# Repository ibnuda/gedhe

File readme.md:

# Gedhe

It's a split columnar-stagger keyboard that I made for one of
the [mahr](https://en.wikipedia.org/wiki/Mahr) for my wife.

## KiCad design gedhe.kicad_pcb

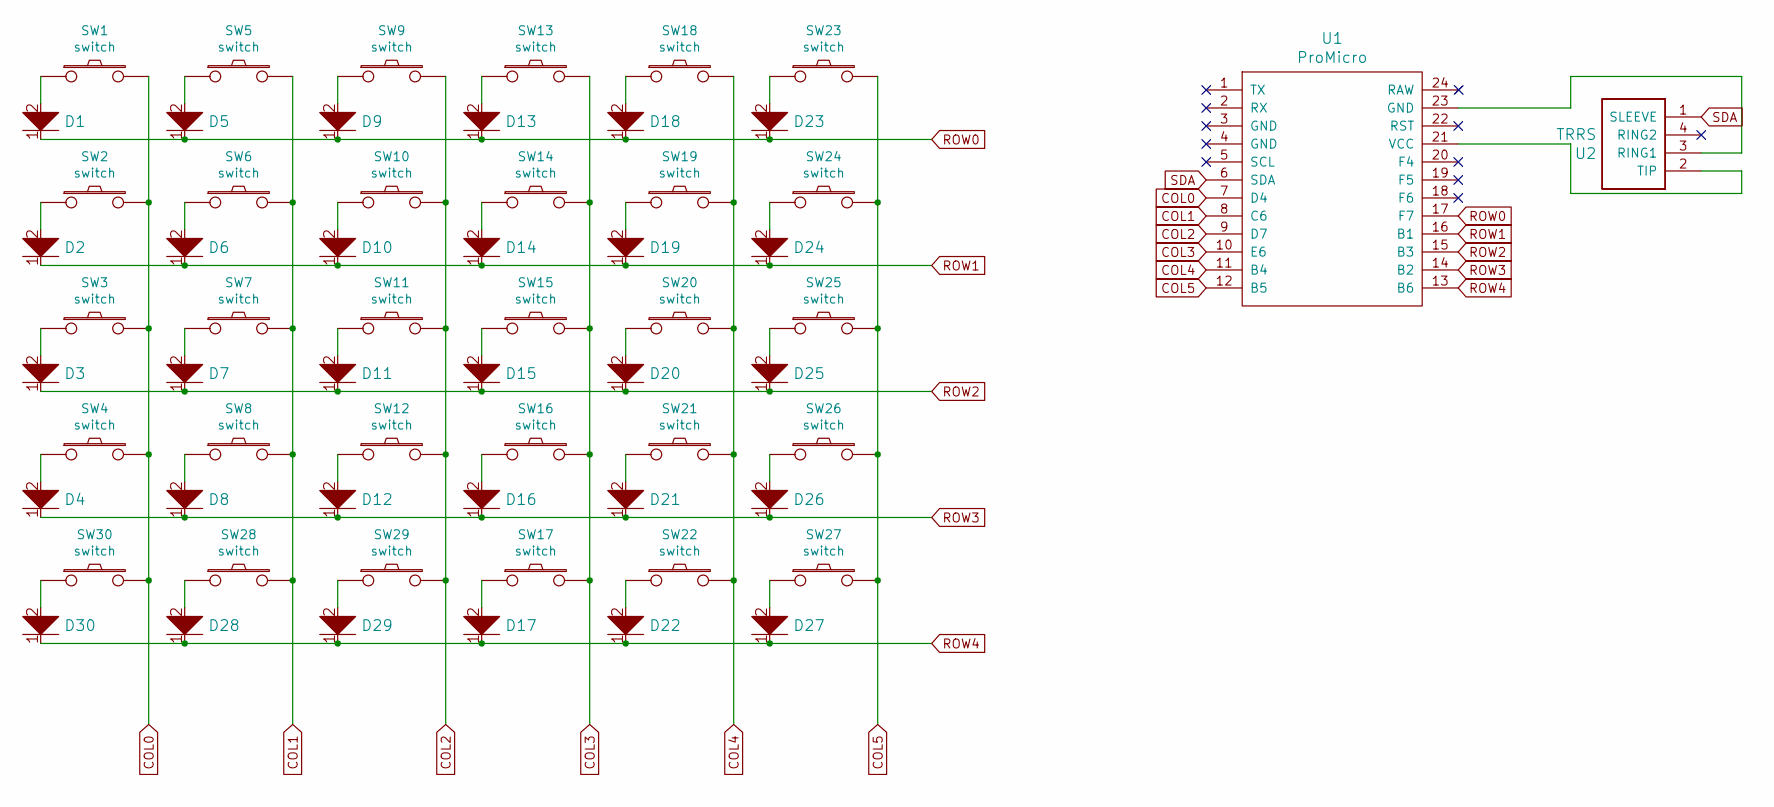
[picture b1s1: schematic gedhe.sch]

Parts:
D1, D2, D3, D4, D5, D6, D7, D8, D9, D10, D11, D12, D13, D14, D15, D16, D17, D18, D19, D20, D21, D22, D23, D24, D25, D26, D27, D28, D29, D30: D; diode
SW1, SW2, SW3, SW4, SW5, SW6, SW7, SW8, SW9, SW10, SW11, SW12, SW13, SW14, SW15, SW16, SW17, SW18, SW19, SW20, SW21, SW22, SW23, SW24, SW25, SW26, SW27, SW28, SW29, SW30: switch; 1u-dual
U1: ProMicro; promicro
U2: TRRS; trrs

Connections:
COL0: SW1.2, SW2.2, SW3.2, SW4.2, SW30.2, U1.7 (D4)
COL1: SW5.2, SW6.2, SW7.2, SW8.2, SW28.2, U1.8 (C6)
COL2: SW9.2, SW10.2, SW11.2, SW12.2, SW29.2, U1.9 (D7)
COL3: SW13.2, SW14.2, SW15.2, SW16.2, SW17.2, U1.10 (E6)
COL4: SW18.2, SW19.2, SW20.2, SW21.2, SW22.2, U1.11 (B4)
COL5: SW23.2, SW24.2, SW25.2, SW26.2, SW27.2, U1.12 (B5)
unnamed: D1.2, SW1.1
unnamed: D2.2, SW2.1
unnamed: D3.2, SW3.1
unnamed: D4.2, SW4.1
unnamed: D5.2, SW5.1
unnamed: D6.2, SW6.1
unnamed: D7.2, SW7.1
unnamed: D8.2, SW8.1
unnamed: D9.2, SW9.1
unnamed: D10.2, SW10.1
unnamed: D11.2, SW11.1
unnamed: D12.2, SW12.1
unnamed: D13.2, SW13.1
unnamed: D14.2, SW14.1
unnamed: D15.2, SW15.1
unnamed: D16.2, SW16.1
unnamed: D17.2, SW17.1
unnamed: D18.2, SW18.1
unnamed: D19.2, SW19.1
unnamed: D20.2, SW20.1
unnamed: D21.2, SW21.1
unnamed: D22.2, SW22.1
unnamed: D23.2, SW23.1
unnamed: D24.2, SW24.1
unnamed: D25.2, SW25.1
unnamed: D26.2, SW26.1
unnamed: D27.2, SW27.1
unnamed: D28.2, SW28.1
unnamed: D29.2, SW29.1
unnamed: D30.2, SW30.1
unnamed: U1.21 (VCC), U2.2 (TIP)
unnamed: U1.23 (GND), U2.3 (RING1)
ROW0: D1.1, D5.1, D9.1, D13.1, D18.1, D23.1, U1.17 (F7)
ROW1: D2.1, D6.1, D10.1, D14.1, D19.1, D24.1, U1.16 (B1)
ROW2: D3.1, D7.1, D11.1, D15.1, D20.1, D25.1, U1.15 (B3)
ROW3: D4.1, D8.1, D12.1, D16.1, D21.1, D26.1, U1.14 (B2)
ROW4: D17.1, D22.1, D27.1, D28.1, D29.1, D30.1, U1.13 (B6)
SDA: U1.6 (SDA), U2.1 (SLEEVE)

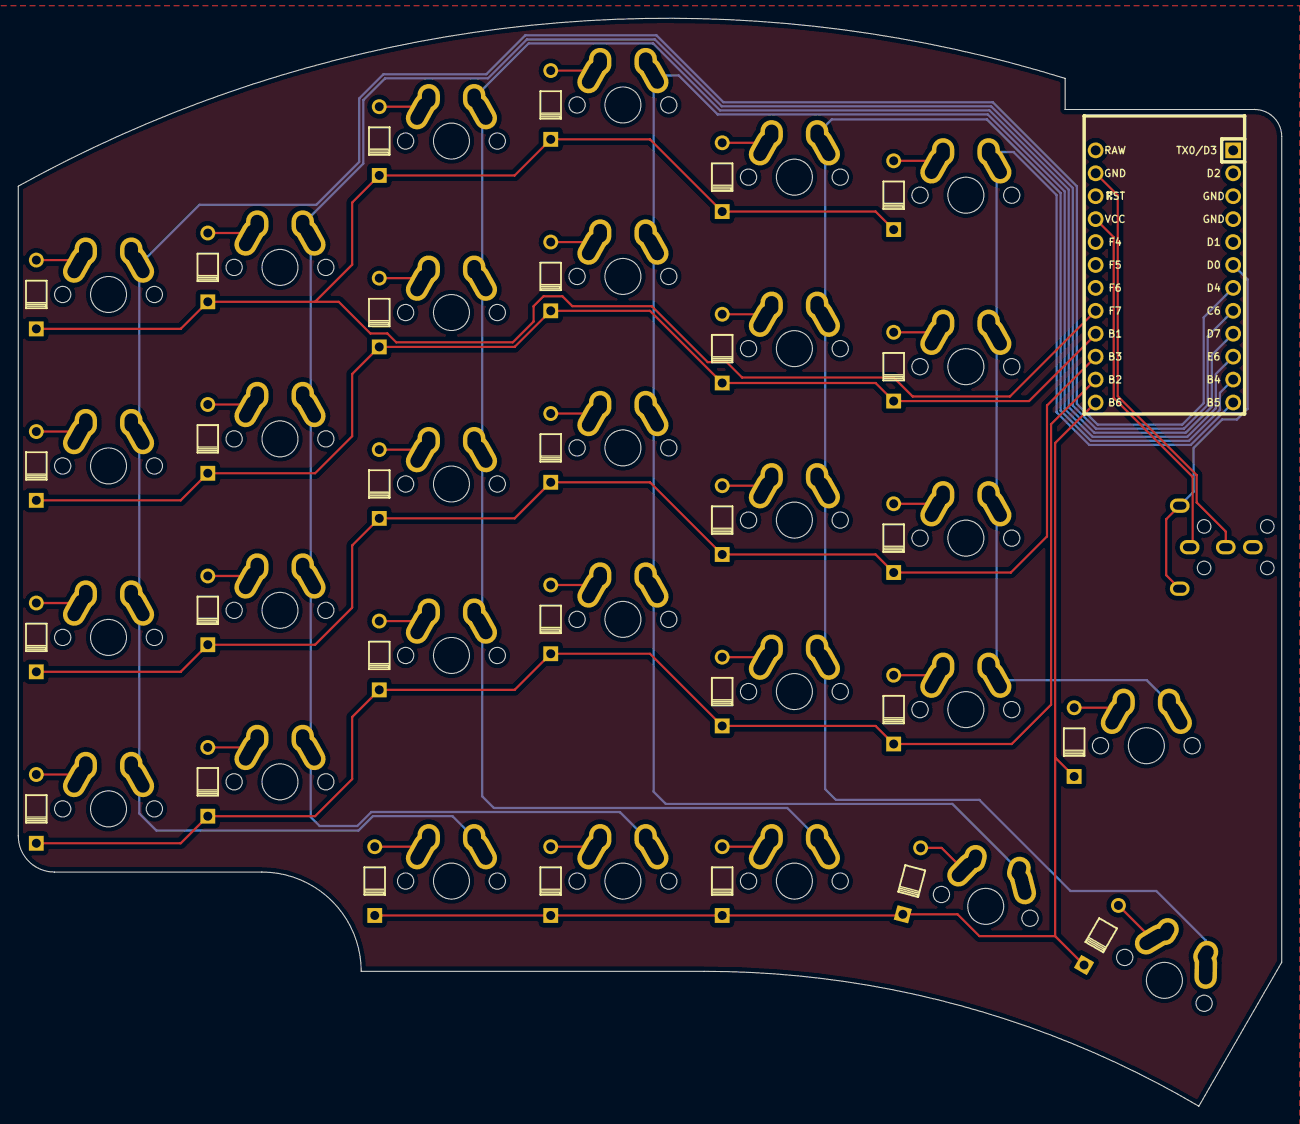
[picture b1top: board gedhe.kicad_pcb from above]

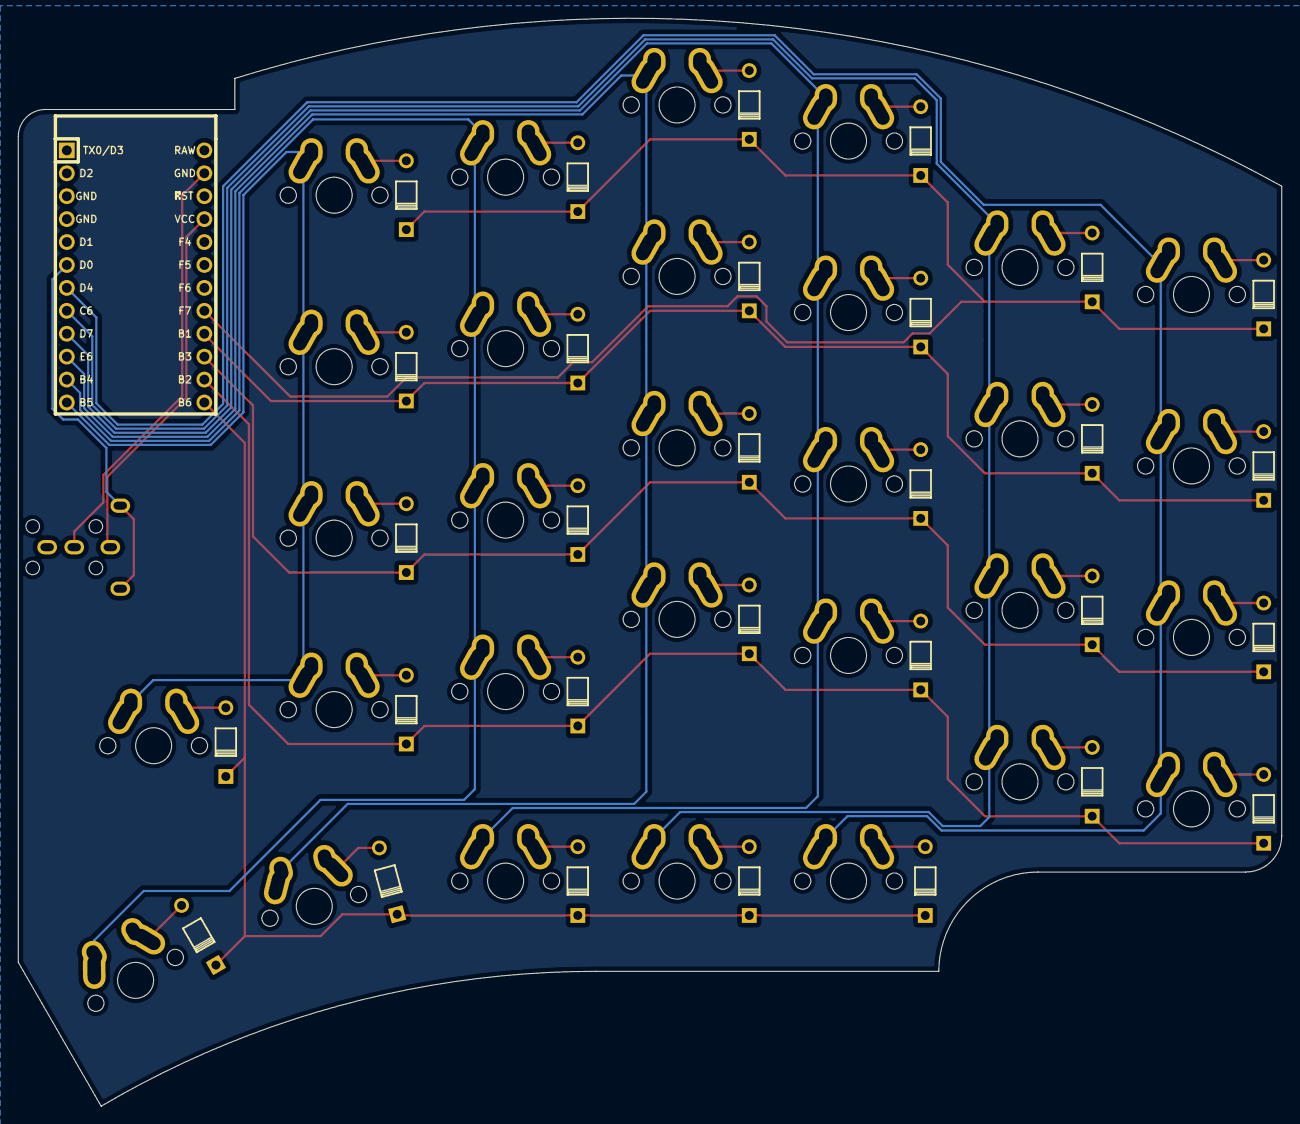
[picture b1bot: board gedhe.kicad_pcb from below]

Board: 2 copper layers, 140.0 x 120.6 mm, 62 parts (2 on the bottom side), 44 nets.

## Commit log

2020-10-05 init commit.
2020-10-11 29 keys per side.
2020-10-12 added key.
2020-10-14 additional key wasn't placed correctly.
2020-11-04 fat bowl case.
2020-11-07 should be around 23mm.
2021-02-22 added a pic.
